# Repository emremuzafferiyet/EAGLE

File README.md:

# EAGLE
WELLCOME MY EAGLE WORLD. MY ATTEMPTS IN HERE TOO.

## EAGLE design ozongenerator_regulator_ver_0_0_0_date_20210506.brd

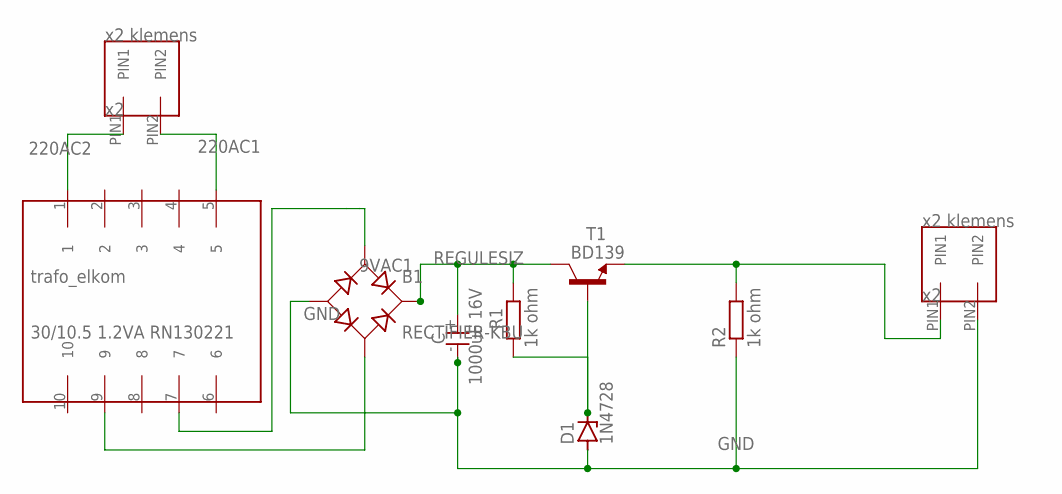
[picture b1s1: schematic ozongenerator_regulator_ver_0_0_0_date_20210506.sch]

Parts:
B1: RECTIFIER-KBU; KBU
D1: 1N4728; DO41Z10
R1, R2: 1k ohm; 0207/12
T1: BD139; TO126
U$1, U$4: X2_KLEMENS
U$2: EL_KOM_TRAFO
U$3: CAPACITOR

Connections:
9VAC1: B1.AC1, U$2.7
220AC1: U$1.PIN2, U$2.5
220AC2: U$1.PIN1, U$2.1
GND: B1.-, D1.A, R2.1, U$3.-, U$4.PIN2
unnamed: R2.2, T1.1 (E), U$4.PIN1
unnamed: D1.C, R1.1, T1.3 (B)
unnamed: B1.AC2, U$2.9
REGULESIZ: B1.+, R1.2, T1.2 (C), U$3.+

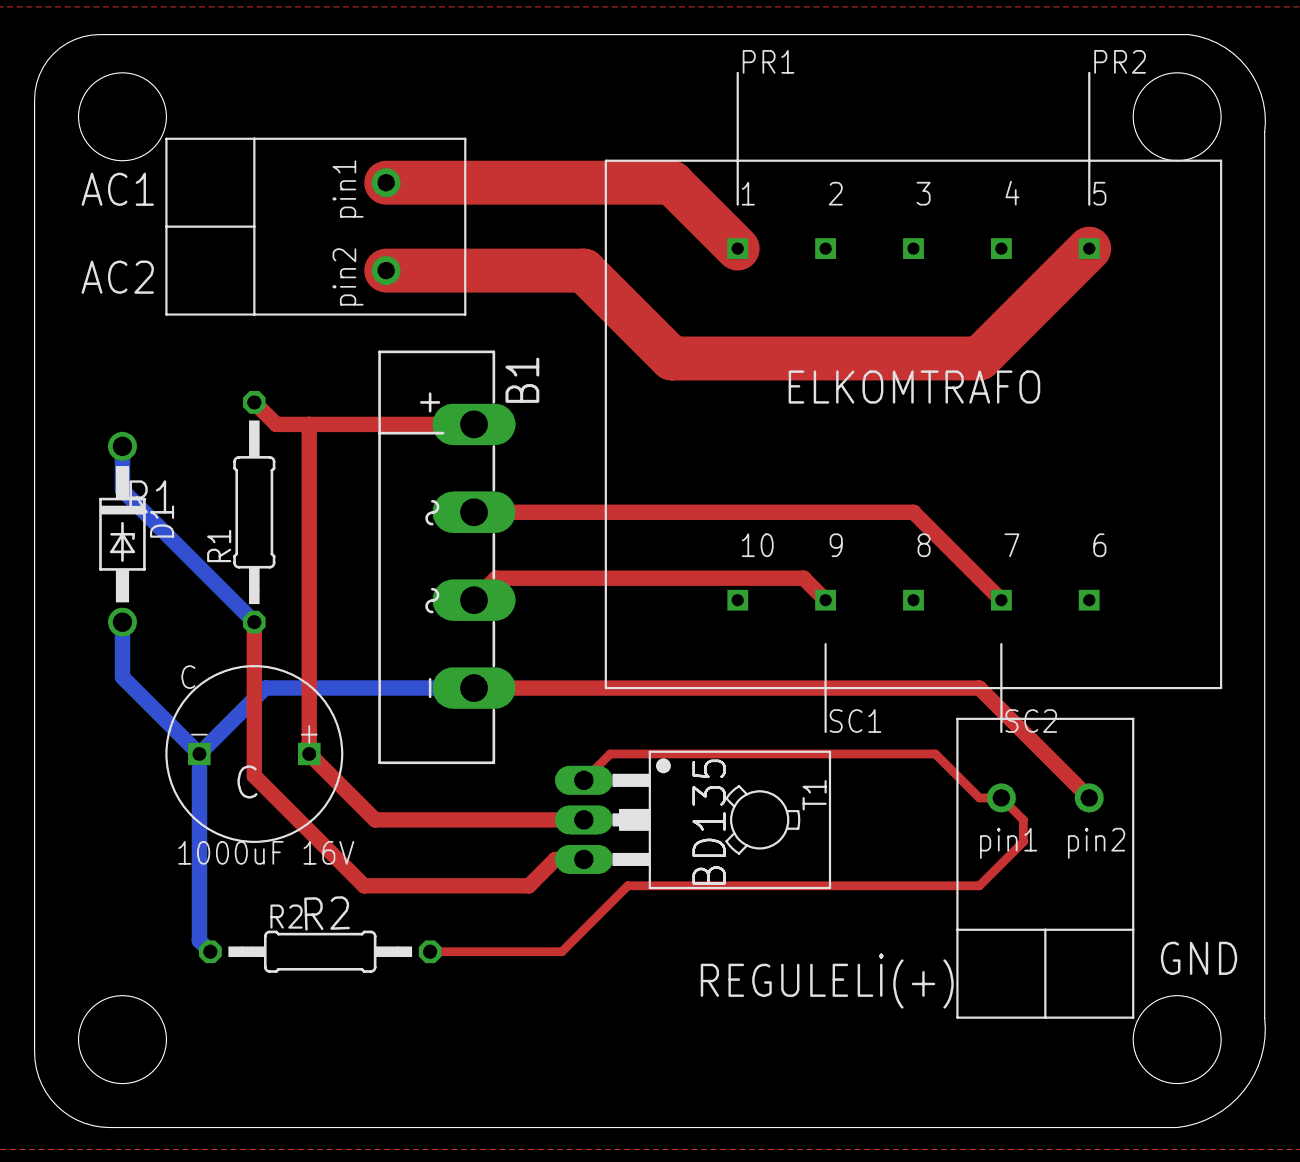
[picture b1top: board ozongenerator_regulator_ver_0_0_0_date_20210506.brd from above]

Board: 2 copper layers, 71.1 x 63.2 mm, 9 parts (0 on the bottom side), 8 nets.

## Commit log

2021-05-28 OZON GENERATOR
    OZON GENERATOR AR GE ATTEMPTS
2021-05-28 ver000
    ver000
